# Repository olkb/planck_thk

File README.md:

# Planck Through Hole Kit

Gerbers and BOMs have been moved to releases:

https://github.com/olkb/planck_thk/releases

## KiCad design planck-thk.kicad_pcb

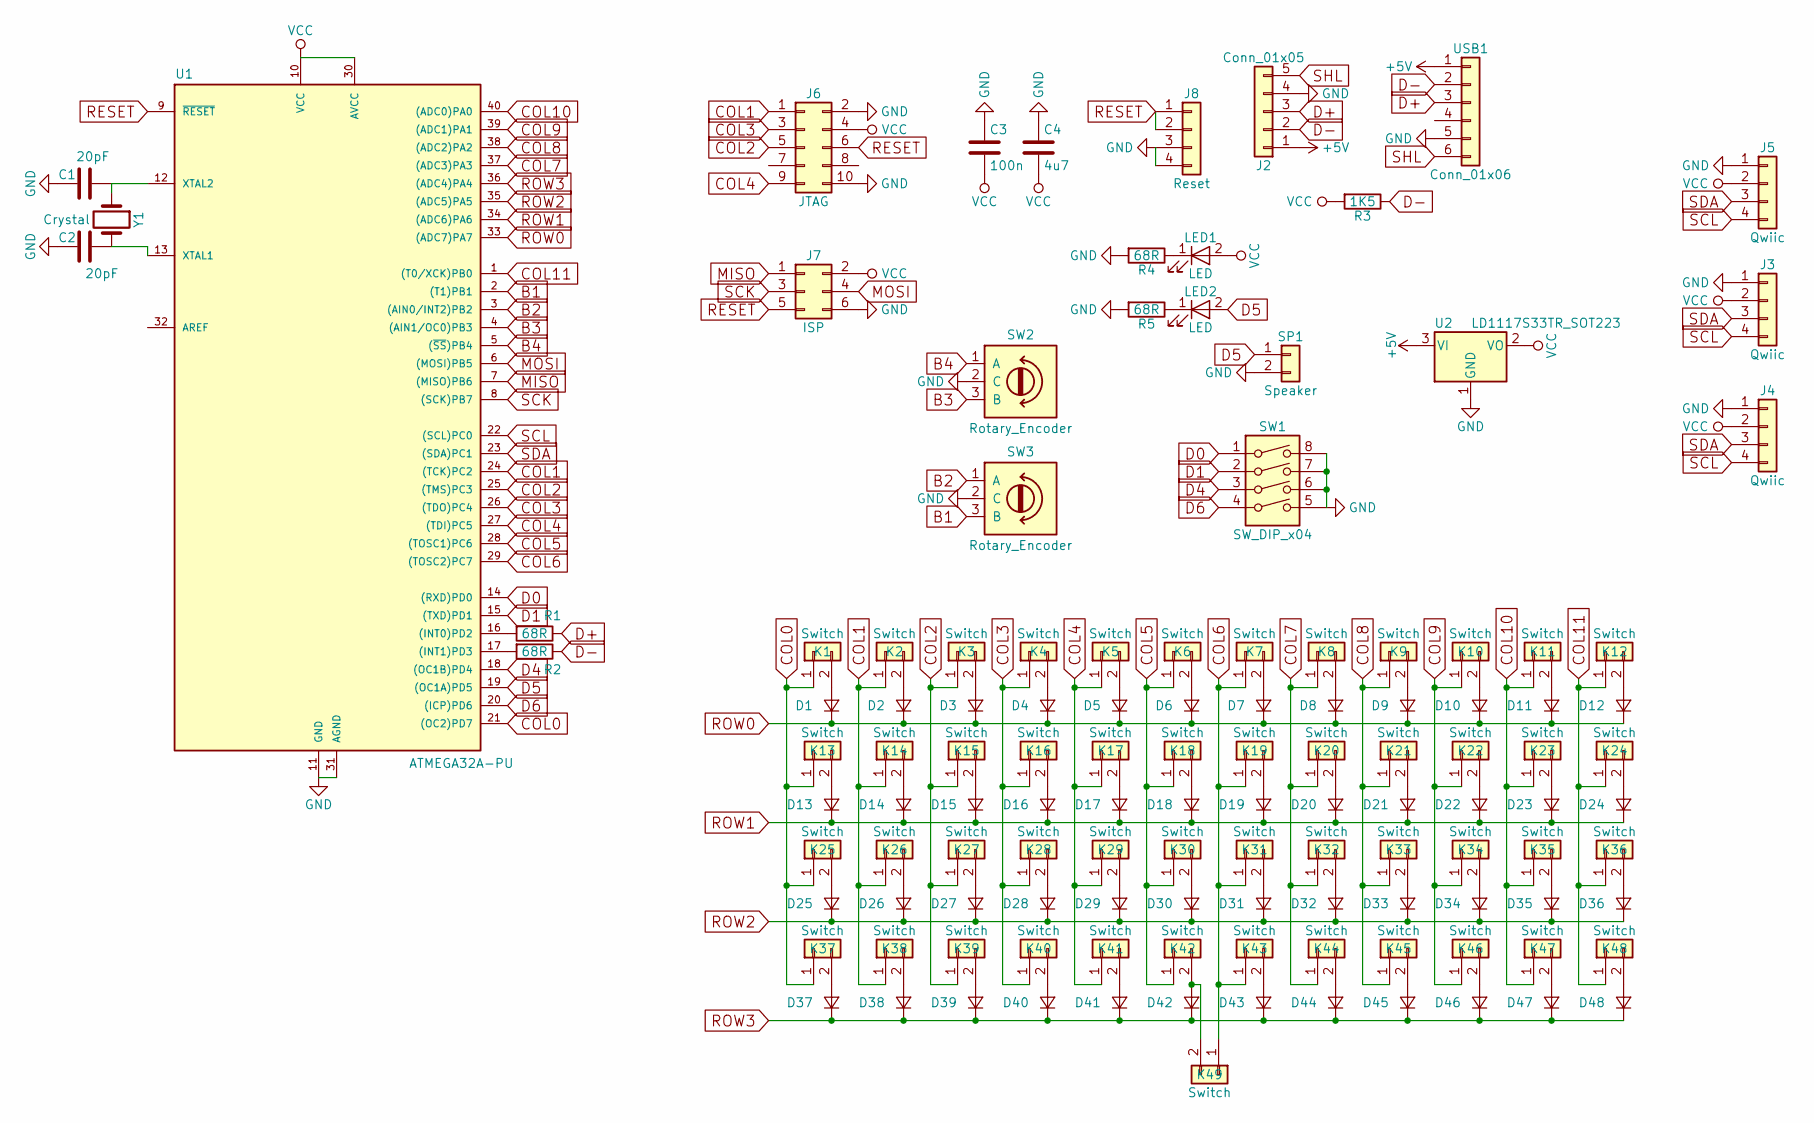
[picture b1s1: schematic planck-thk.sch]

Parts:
C1, C2: 20pF; C_Disc_D3.8mm_W2.6mm_P2.50mm
C3: 100n; C_Disc_D3.8mm_W2.6mm_P2.50mm
C4: 4u7; C_Disc_D3.8mm_W2.6mm_P2.50mm
D1, D2, D3, D4, D5, D6, D7, D8, D9, D10, D11, D12, D13, D14, D15, D16, D17, D18, D19, D20, D21, D22, D23, D24, D25, D26, D27, D28, D29, D30, D31, D32, D33, D34, D35, D36, D37, D38, D39, D40, D41, D42, D43, D44, D45, D46, D47, D48: D; D_DO-35_SOD27_P7.62mm_Horizontal
J2: Conn_01x05; JST_PH_S5B-PH-K_05x2.00mm_Angled
J3, J4, J5: Qwiic; JST_SH_SM04B-SRSS-TB_04x1.00mm_Angled-SZ-combined
J6: JTAG; Pin_Header_Straight_2x05_Pitch2.54mm
J7: ISP; Pin_Header_Straight_2x03_Pitch2.54mm
J8: Reset; 1302-9303
K1, K2, K3, K4, K5, K6, K7, K8, K9, K10, K11, K12, K13, K14, K15, K16, K17, K18, K19, K20, K21, K22, K23, K24, K25, K26, K27, K28, K29, K30, K31, K32, K33, K34, K35, K36, K37, K38, K39, K40, K41, K42, K43, K44, K45, K46, K47, K48, K49: Switch; UniKBSwitch_1u
LED1, LED2: LED; LED_D3.0mm
R1, R2, R4, R5: 68R; R_Axial_DIN0204_L3.6mm_D1.6mm_P7.62mm_Horizontal
R3: 1K5; R_Axial_DIN0204_L3.6mm_D1.6mm_P7.62mm_Horizontal
SP1: Speaker
SW1: SW_DIP_x04; 210-4ES
SW2, SW3: Rotary_Encoder; PEC12R-4XXXF-NXXXX
U1: ATMEGA32A-PU; DIP-40_W15.24mm_Socket_LongPads
U2: LD1117S33TR_SOT223; TO-220-3_Horizontal
USB1: Conn_01x06
Y1: Crystal; Crystal_HC49-U_Vertical

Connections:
+5V: J2.1, U2.3 (VI), USB1.1
B1: SW3.3 (B), U1.2 ((T1)PB1)
B2: SW3.1 (A), U1.3 ((AIN0/INT2)PB2)
B3: SW2.3 (B), U1.4 ((AIN1/OC0)PB3)
B4: SW2.1 (A), U1.5 ((~SS~)PB4)
COL0: K1.1, K13.1, K25.1, K37.1, U1.21 ((OC2)PD7)
COL1: J6.1, K2.1, K14.1, K26.1, K38.1, U1.24 ((TCK)PC2)
COL2: J6.5, K3.1, K15.1, K27.1, K39.1, U1.25 ((TMS)PC3)
COL3: J6.3, K4.1, K16.1, K28.1, K40.1, U1.26 ((TDO)PC4)
COL4: J6.9, K5.1, K17.1, K29.1, K41.1, U1.27 ((TDI)PC5)
COL5: K6.1, K18.1, K30.1, K42.1, U1.28 ((TOSC1)PC6)
COL6: K7.1, K19.1, K31.1, K43.1, K49.1, U1.29 ((TOSC2)PC7)
COL7: K8.1, K20.1, K32.1, K44.1, U1.37 ((ADC3)PA3)
COL8: K9.1, K21.1, K33.1, K45.1, U1.38 ((ADC2)PA2)
COL9: K10.1, K22.1, K34.1, K46.1, U1.39 ((ADC1)PA1)
COL10: K11.1, K23.1, K35.1, K47.1, U1.40 ((ADC0)PA0)
COL11: K12.1, K24.1, K36.1, K48.1, U1.1 ((T0/XCK)PB0)
D0: SW1.1, U1.14 ((RXD)PD0)
D1: SW1.2, U1.15 ((TXD)PD1)
D4: SW1.3, U1.18 ((OC1B)PD4)
D5: LED2.2 (A), SP1.1, U1.19 ((OC1A)PD5)
D6: SW1.4, U1.20 ((ICP)PD6)
D+: J2.3, R1.1, USB1.3
D-: J2.2, R2.1, R3.1, USB1.2
GND: C1.2, C2.2, C3.1, C4.1, J2.4, J3.1, J4.1, J5.1, J6.2, J6.10, J7.6, J8.3, J8.4, R4.2, R5.2, SP1.2, SW1.5, SW1.6, SW1.7, SW1.8, SW2.2 (C), SW3.2 (C), U1.11 (GND), U1.31 (AGND), U2.1 (GND), USB1.5
MISO: J7.1, U1.7 ((MISO)PB6)
MOSI: J7.4, U1.6 ((MOSI)PB5)
unnamed: C1.1, U1.12 (XTAL2), Y1.1
unnamed: C2.1, U1.13 (XTAL1), Y1.2
unnamed: D1.2 (A), K1.2
unnamed: D2.2 (A), K2.2
unnamed: D3.2 (A), K3.2
unnamed: D4.2 (A), K4.2
unnamed: D5.2 (A), K5.2
unnamed: D6.2 (A), K6.2
unnamed: D7.2 (A), K7.2
unnamed: D8.2 (A), K8.2
unnamed: D9.2 (A), K9.2
unnamed: D10.2 (A), K10.2
unnamed: D11.2 (A), K11.2
unnamed: D12.2 (A), K12.2
unnamed: D13.2 (A), K13.2
unnamed: D14.2 (A), K14.2
unnamed: D15.2 (A), K15.2
unnamed: D16.2 (A), K16.2
unnamed: D17.2 (A), K17.2
unnamed: D18.2 (A), K18.2
unnamed: D19.2 (A), K19.2
unnamed: D20.2 (A), K20.2
unnamed: D21.2 (A), K21.2
unnamed: D22.2 (A), K22.2
unnamed: D23.2 (A), K23.2
unnamed: D24.2 (A), K24.2
unnamed: D25.2 (A), K25.2
unnamed: D26.2 (A), K26.2
unnamed: D27.2 (A), K27.2
unnamed: D28.2 (A), K28.2
unnamed: D29.2 (A), K29.2
unnamed: D30.2 (A), K30.2
unnamed: D31.2 (A), K31.2
unnamed: D32.2 (A), K32.2
unnamed: D33.2 (A), K33.2
unnamed: D34.2 (A), K34.2
unnamed: D35.2 (A), K35.2
unnamed: D36.2 (A), K36.2
unnamed: D37.2 (A), K37.2
unnamed: D38.2 (A), K38.2
unnamed: D39.2 (A), K39.2
unnamed: D40.2 (A), K40.2
unnamed: D41.2 (A), K41.2
unnamed: D42.2 (A), K42.2, K49.2
unnamed: D43.2 (A), K43.2
unnamed: D44.2 (A), K44.2
unnamed: D45.2 (A), K45.2
unnamed: D46.2 (A), K46.2
unnamed: D47.2 (A), K47.2
unnamed: D48.2 (A), K48.2
unnamed: LED1.1 (K), R4.1
unnamed: LED2.1 (K), R5.1
unnamed: R1.2, U1.16 ((INT0)PD2)
unnamed: R2.2, U1.17 ((INT1)PD3)
RESET: J6.6, J7.5, J8.1, J8.2, U1.9 (~RESET)
ROW0: D1.1 (K), D2.1 (K), D3.1 (K), D4.1 (K), D5.1 (K), D6.1 (K), D7.1 (K), D8.1 (K), D9.1 (K), D10.1 (K), D11.1 (K), D12.1 (K), U1.33 ((ADC7)PA7)
ROW1: D13.1 (K), D14.1 (K), D15.1 (K), D16.1 (K), D17.1 (K), D18.1 (K), D19.1 (K), D20.1 (K), D21.1 (K), D22.1 (K), D23.1 (K), D24.1 (K), U1.34 ((ADC6)PA6)
ROW2: D25.1 (K), D26.1 (K), D27.1 (K), D28.1 (K), D29.1 (K), D30.1 (K), D31.1 (K), D32.1 (K), D33.1 (K), D34.1 (K), D35.1 (K), D36.1 (K), U1.35 ((ADC5)PA5)
ROW3: D37.1 (K), D38.1 (K), D39.1 (K), D40.1 (K), D41.1 (K), D42.1 (K), D43.1 (K), D44.1 (K), D45.1 (K), D46.1 (K), D47.1 (K), D48.1 (K), U1.36 ((ADC4)PA4)
SCK: J7.3, U1.8 ((SCK)PB7)
SCL: J3.4, J4.4, J5.4, U1.22 ((SCL)PC0)
SDA: J3.3, J4.3, J5.3, U1.23 ((SDA)PC1)
SHL: J2.5, USB1.6
VCC: C3.2, C4.2, J3.2, J4.2, J5.2, J6.4, J7.2, LED1.2 (A), R3.2, U1.10 (VCC), U1.30 (AVCC), U2.2 (VO)

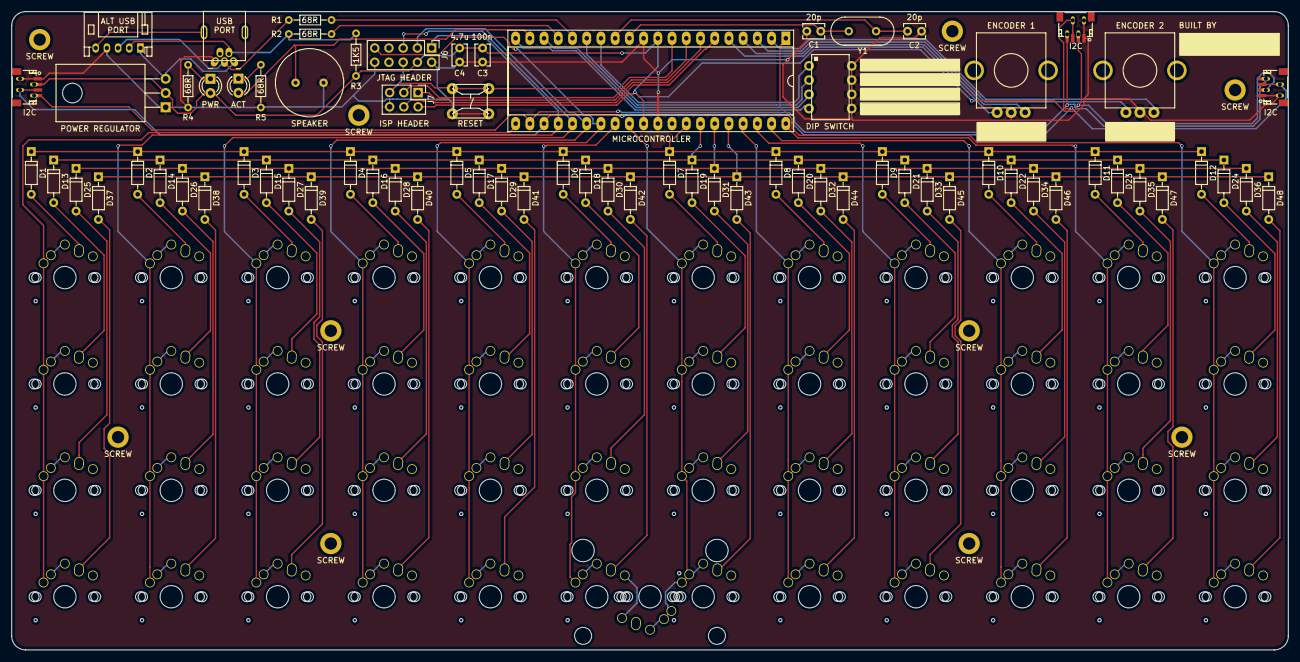
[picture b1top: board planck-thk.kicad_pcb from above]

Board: 2 copper layers, 228.0 x 114.0 mm, 124 parts (0 on the bottom side), 91 nets.

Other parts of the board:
MX-cut1: MX-stab; MX_2U_cutouts

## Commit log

2018-10-30 fix isp and jtag, usb port, remove gerbers
2018-10-31 update readme, holes sizes
